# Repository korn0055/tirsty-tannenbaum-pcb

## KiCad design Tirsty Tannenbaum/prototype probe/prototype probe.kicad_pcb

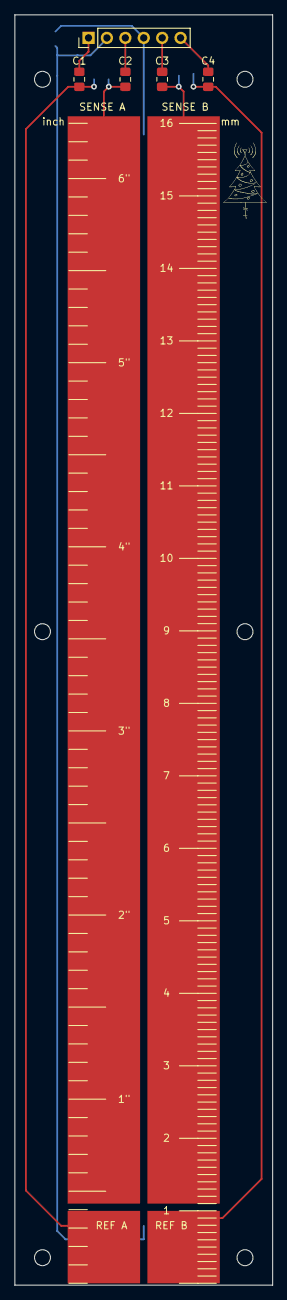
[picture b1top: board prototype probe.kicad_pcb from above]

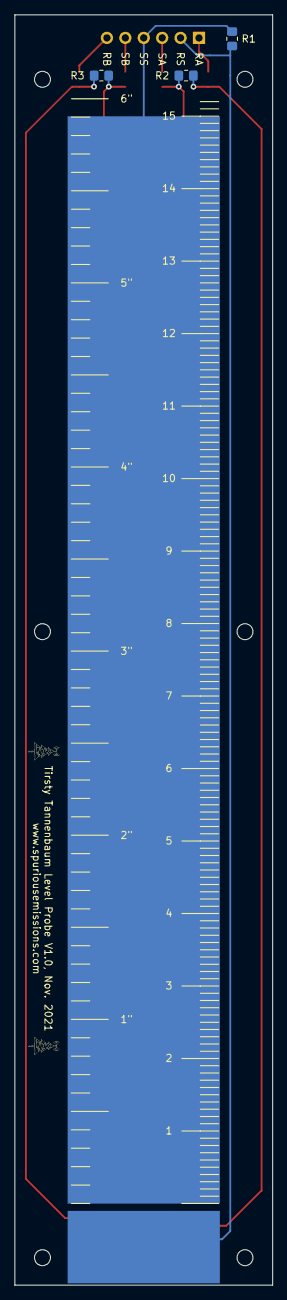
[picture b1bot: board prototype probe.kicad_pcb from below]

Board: 2 copper layers, 35.6 x 175.2 mm, 16 parts (3 on the bottom side), 10 nets.

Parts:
C1, C2, C3, C4: C; C_0805_2012Metric_Pad1.18x1.45mm_HandSolder
H1, H2, H3, H4, H5, H6: MountingHole; MountingHole_2.2mm_M2
J1: Conn_01x06_Male; PinHeader_1x06_P2.54mm_Vertical
J2: Conn_01x03_Male; Cap-Electrode
J3: Conn_01x03_Male; Cap-Electrode-Dielectric-Comp
R1, R2, R3: R; R_0805_2012Metric_Pad1.20x1.40mm_HandSolder

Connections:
unnamed: C1.1, J3.1, R2.2
unnamed: C1.2, J1.1
unnamed: C2.1, J2.1, R2.1
unnamed: C2.2, J1.3
unnamed: C3.1, J2.2, R3.2
unnamed: C3.2, J1.5
unnamed: C4.1, J3.2, R3.1
unnamed: C4.2, J1.6
unnamed: J1.2, J3.3, R1.1
unnamed: J1.4, J2.3, R1.2

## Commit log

2021-11-17 Add prototype probe layout - needs silk
2021-11-18 Made dielectric comp section inline to save PCB costs, added option for inline ref caps
2021-11-19 Silkscreen ruler in progress
2021-11-19 Finished ruler
2021-11-20 Add ruler to bottom side
2021-11-20 Add logo
2022-11-15 Convert to KiCad 6
2022-11-24 Update schematic to 6.0?
